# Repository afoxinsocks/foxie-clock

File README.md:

# Foxie Clock

## A Nixie-like, retro, RGB LED, Arduino-powered clock

Welcome to the Foxie Clock, a fully open-source RGB clock with nixie-like edge-lit acrylic digits. Or... an RGB pixel display clock, if you like!

## Looks

With a look inspired by old nixie tubes and with capacitors protruding through the surface like vacuum tubes, the Foxie Clock is a fun, colorful way to display the time at your desk, office, or anywhere. Brightness, color, and time are all adjustable directly with 4 buttons on the back. [Using the clock is very easy](USAGE.md), with 4 buttons on the back providing various functionality for setting time, animation modes, colors, and brightness, 12/24h mode, PXL mode, and more.

# [Get your own](https://www.foxieproducts.com/)

Head [over to Foxie Products](https://www.foxieproducts.com/) to order your own Foxie Clock kit.

## 3D Print your own case or modify it yourself!

All .STL models and the full Fusion360 project and the .step files are also available for anyone wanting to make changes to the design more easily. Head over to [Thingiverse](https://www.thingiverse.com/thing:4114349) to download.

## Easy to assemble

The clock is [easy to assemble](ASSEMBLY.md) and looks beautiful when complete.

The case is 3D printed and is included with the kit.

The circuit board can be ordered fully soldered, or if you like, you can solder the 4 buttons and RedBoard Nano yourself, using the plentiful pictures in the [electronics assembly guide](ELECTRONICS.md).

## Easy to hack

The Foxie Clock is powered by a SparkFun RedBoard Artemis Nano (https://www.sparkfun.com/products/15443), an extremely cool, fully Arduino-compatible board that supports Bluetooth LE 5.0 and much, much more. It is included in every Foxie Clock kit, along with everything you need (including USB-C cable) to get running.

## Fully Open Source

The Foxie Clock PCB and firmware were developed using Open Source software. The source code, laser cutting files, PCB design, and documentation for assembly are all freely available here.

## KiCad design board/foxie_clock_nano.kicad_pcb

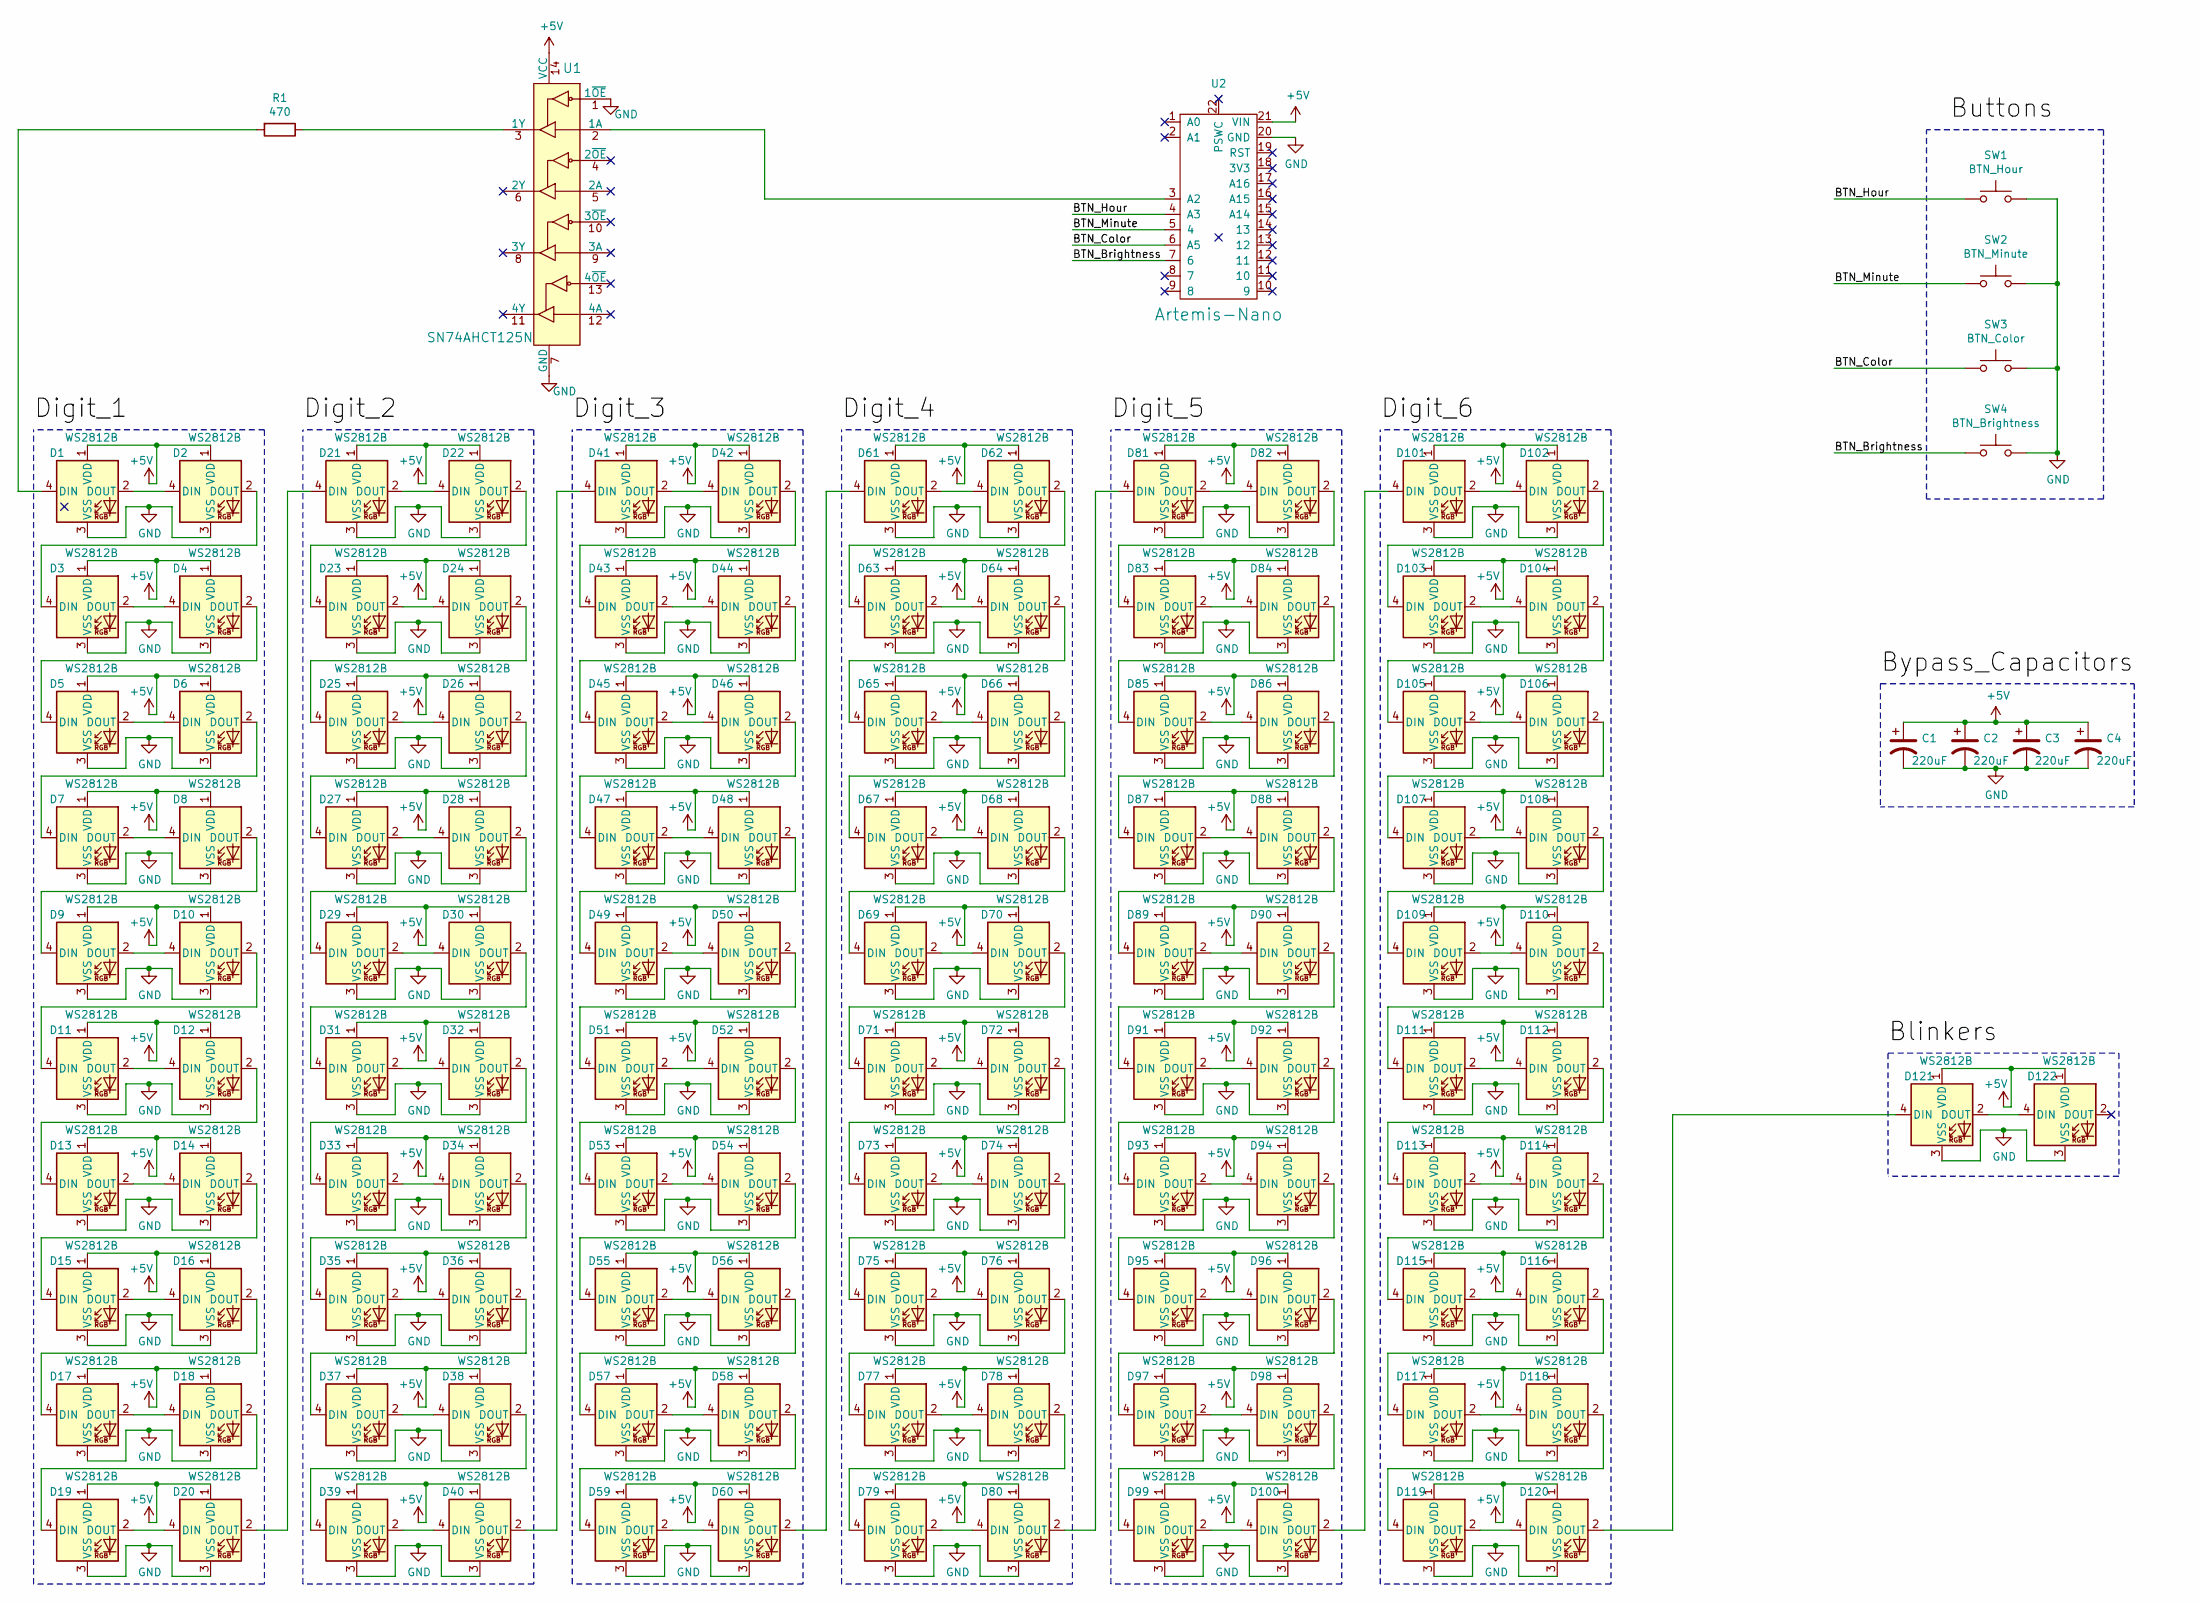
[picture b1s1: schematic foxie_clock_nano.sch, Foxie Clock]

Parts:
C1, C2, C3, C4: 220uF; CP_Elec_6.3x7.7; LCSC C127327
D1, D2, D3, D4, D5, D6, D7, D8, D9, D10, D11, D12, D13, D14, D15, D16, D17, D18, D19, D20, D21, D22, D23, D24, D25, D26, D27, D28, D29, D30, D31, D32, D33, D34, D35, D36, D37, D38, D39, D40, D41, D42, D43, D44, D45, D46, D47, D48, D49, D50, D51, D52, D53, D54, D55, D56, D57, D58, D59, D60, D61, D62, D63, D64, D65, D66, D67, D68, D69, D70, D71, D72, D73, D74, D75, D76, D77, D78, D79, D80, D81, D82, D83, D84, D85, D86, D87, D88, D89, D90, D91, D92, D93, D94, D95, D96, D97, D98, D99, D100, D101, D102, D103, D104, D105, D106, D107, D108, D109, D110, D111, D112, D113, D114, D115, D116, D117, D118, D119, D120, D121, D122: WS2812B; LED_WS2812B_PLCC4_5.0x5.0mm_P3.2mm; LCSC C114586
R1: 470; R_1206_3216Metric; LCSC C25383
SW1: BTN_Hour; SW_Tactile_SPST_Angled_PTS645Vx58-2LFS
SW2: BTN_Minute; SW_Tactile_SPST_Angled_PTS645Vx58-2LFS
SW3: BTN_Color; SW_Tactile_SPST_Angled_PTS645Vx58-2LFS
SW4: BTN_Brightness; SW_Tactile_SPST_Angled_PTS645Vx58-2LFS
U1: SN74AHCT125N; TSSOP-14_4.4x5mm_P0.65mm; LCSC C36365
U2: Artemis-Nano

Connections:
+5V: C1.1, C2.1, C3.1, C4.1, D1.1 (VDD), D2.1 (VDD), D3.1 (VDD), D4.1 (VDD), D5.1 (VDD), D6.1 (VDD), D7.1 (VDD), D8.1 (VDD), D9.1 (VDD), D10.1 (VDD), D11.1 (VDD), D12.1 (VDD), D13.1 (VDD), D14.1 (VDD), D15.1 (VDD), D16.1 (VDD), D17.1 (VDD), D18.1 (VDD), D19.1 (VDD), D20.1 (VDD), D21.1 (VDD), D22.1 (VDD), D23.1 (VDD), D24.1 (VDD), D25.1 (VDD), D26.1 (VDD), D27.1 (VDD), D28.1 (VDD), D29.1 (VDD), D30.1 (VDD), D31.1 (VDD), D32.1 (VDD), D33.1 (VDD), D34.1 (VDD), D35.1 (VDD), D36.1 (VDD), D37.1 (VDD), D38.1 (VDD), D39.1 (VDD), D40.1 (VDD), D41.1 (VDD), D42.1 (VDD), D43.1 (VDD), D44.1 (VDD), D45.1 (VDD), D46.1 (VDD), D47.1 (VDD), D48.1 (VDD), D49.1 (VDD), D50.1 (VDD), D51.1 (VDD), D52.1 (VDD), D53.1 (VDD), D54.1 (VDD), D55.1 (VDD), D56.1 (VDD), D57.1 (VDD), D58.1 (VDD), D59.1 (VDD), D60.1 (VDD), D61.1 (VDD), D62.1 (VDD), D63.1 (VDD), D64.1 (VDD), D65.1 (VDD), D66.1 (VDD), D67.1 (VDD), D68.1 (VDD), D69.1 (VDD), D70.1 (VDD), D71.1 (VDD), D72.1 (VDD), D73.1 (VDD), D74.1 (VDD), D75.1 (VDD), D76.1 (VDD), D77.1 (VDD), D78.1 (VDD), D79.1 (VDD), D80.1 (VDD), D81.1 (VDD), D82.1 (VDD), D83.1 (VDD), D84.1 (VDD), D85.1 (VDD), D86.1 (VDD), D87.1 (VDD), D88.1 (VDD), D89.1 (VDD), D90.1 (VDD), D91.1 (VDD), D92.1 (VDD), D93.1 (VDD), D94.1 (VDD), D95.1 (VDD), D96.1 (VDD), D97.1 (VDD), D98.1 (VDD), D99.1 (VDD), D100.1 (VDD), D101.1 (VDD), D102.1 (VDD), D103.1 (VDD), D104.1 (VDD), D105.1 (VDD), D106.1 (VDD), D107.1 (VDD), D108.1 (VDD), D109.1 (VDD), D110.1 (VDD), D111.1 (VDD), D112.1 (VDD), D113.1 (VDD), D114.1 (VDD), D115.1 (VDD), D116.1 (VDD), D117.1 (VDD), D118.1 (VDD), D119.1 (VDD), D120.1 (VDD), D121.1 (VDD), D122.1 (VDD), U1.14 (VCC), U2.21 (VIN)
/BTN_Brightness: SW4.1, U2.7 (6)
/BTN_Color: SW3.1, U2.6 (A5)
/BTN_Hour: SW1.1, U2.4 (A3)
/BTN_Minute: SW2.1, U2.5 (4)
GND: C1.2, C2.2, C3.2, C4.2, D1.3 (VSS), D2.3 (VSS), D3.3 (VSS), D4.3 (VSS), D5.3 (VSS), D6.3 (VSS), D7.3 (VSS), D8.3 (VSS), D9.3 (VSS), D10.3 (VSS), D11.3 (VSS), D12.3 (VSS), D13.3 (VSS), D14.3 (VSS), D15.3 (VSS), D16.3 (VSS), D17.3 (VSS), D18.3 (VSS), D19.3 (VSS), D20.3 (VSS), D21.3 (VSS), D22.3 (VSS), D23.3 (VSS), D24.3 (VSS), D25.3 (VSS), D26.3 (VSS), D27.3 (VSS), D28.3 (VSS), D29.3 (VSS), D30.3 (VSS), D31.3 (VSS), D32.3 (VSS), D33.3 (VSS), D34.3 (VSS), D35.3 (VSS), D36.3 (VSS), D37.3 (VSS), D38.3 (VSS), D39.3 (VSS), D40.3 (VSS), D41.3 (VSS), D42.3 (VSS), D43.3 (VSS), D44.3 (VSS), D45.3 (VSS), D46.3 (VSS), D47.3 (VSS), D48.3 (VSS), D49.3 (VSS), D50.3 (VSS), D51.3 (VSS), D52.3 (VSS), D53.3 (VSS), D54.3 (VSS), D55.3 (VSS), D56.3 (VSS), D57.3 (VSS), D58.3 (VSS), D59.3 (VSS), D60.3 (VSS), D61.3 (VSS), D62.3 (VSS), D63.3 (VSS), D64.3 (VSS), D65.3 (VSS), D66.3 (VSS), D67.3 (VSS), D68.3 (VSS), D69.3 (VSS), D70.3 (VSS), D71.3 (VSS), D72.3 (VSS), D73.3 (VSS), D74.3 (VSS), D75.3 (VSS), D76.3 (VSS), D77.3 (VSS), D78.3 (VSS), D79.3 (VSS), D80.3 (VSS), D81.3 (VSS), D82.3 (VSS), D83.3 (VSS), D84.3 (VSS), D85.3 (VSS), D86.3 (VSS), D87.3 (VSS), D88.3 (VSS), D89.3 (VSS), D90.3 (VSS), D91.3 (VSS), D92.3 (VSS), D93.3 (VSS), D94.3 (VSS), D95.3 (VSS), D96.3 (VSS), D97.3 (VSS), D98.3 (VSS), D99.3 (VSS), D100.3 (VSS), D101.3 (VSS), D102.3 (VSS), D103.3 (VSS), D104.3 (VSS), D105.3 (VSS), D106.3 (VSS), D107.3 (VSS), D108.3 (VSS), D109.3 (VSS), D110.3 (VSS), D111.3 (VSS), D112.3 (VSS), D113.3 (VSS), D114.3 (VSS), D115.3 (VSS), D116.3 (VSS), D117.3 (VSS), D118.3 (VSS), D119.3 (VSS), D120.3 (VSS), D121.3 (VSS), D122.3 (VSS), SW1.2, SW2.2, SW3.2, SW4.2, U1.1 (1~OE), U1.7 (GND), U2.20 (GND)
unnamed: D1.2 (DOUT), D2.4 (DIN)
unnamed: D1.4 (DIN), R1.2
unnamed: D2.2 (DOUT), D3.4 (DIN)
unnamed: D3.2 (DOUT), D4.4 (DIN)
unnamed: D4.2 (DOUT), D5.4 (DIN)
unnamed: D5.2 (DOUT), D6.4 (DIN)
unnamed: D6.2 (DOUT), D7.4 (DIN)
unnamed: D7.2 (DOUT), D8.4 (DIN)
unnamed: D8.2 (DOUT), D9.4 (DIN)
unnamed: D10.2 (DOUT), D11.4 (DIN)
unnamed: D9.2 (DOUT), D10.4 (DIN)
unnamed: D11.2 (DOUT), D12.4 (DIN)
unnamed: D12.2 (DOUT), D13.4 (DIN)
unnamed: D13.2 (DOUT), D14.4 (DIN)
unnamed: D14.2 (DOUT), D15.4 (DIN)
unnamed: D15.2 (DOUT), D16.4 (DIN)
unnamed: D16.2 (DOUT), D17.4 (DIN)
unnamed: D17.2 (DOUT), D18.4 (DIN)
unnamed: D18.2 (DOUT), D19.4 (DIN)
unnamed: D19.2 (DOUT), D20.4 (DIN)
unnamed: D20.2 (DOUT), D21.4 (DIN)
unnamed: D21.2 (DOUT), D22.4 (DIN)
unnamed: D22.2 (DOUT), D23.4 (DIN)
unnamed: D23.2 (DOUT), D24.4 (DIN)
unnamed: D24.2 (DOUT), D25.4 (DIN)
unnamed: D25.2 (DOUT), D26.4 (DIN)
unnamed: D26.2 (DOUT), D27.4 (DIN)
unnamed: D27.2 (DOUT), D28.4 (DIN)
unnamed: D28.2 (DOUT), D29.4 (DIN)
unnamed: D29.2 (DOUT), D30.4 (DIN)
unnamed: D30.2 (DOUT), D31.4 (DIN)
unnamed: D31.2 (DOUT), D32.4 (DIN)
unnamed: D32.2 (DOUT), D33.4 (DIN)
unnamed: D33.2 (DOUT), D34.4 (DIN)
unnamed: D34.2 (DOUT), D35.4 (DIN)
unnamed: D35.2 (DOUT), D36.4 (DIN)
unnamed: D36.2 (DOUT), D37.4 (DIN)
unnamed: D37.2 (DOUT), D38.4 (DIN)
unnamed: D38.2 (DOUT), D39.4 (DIN)
unnamed: D39.2 (DOUT), D40.4 (DIN)
unnamed: D40.2 (DOUT), D41.4 (DIN)
unnamed: D41.2 (DOUT), D42.4 (DIN)
unnamed: D42.2 (DOUT), D43.4 (DIN)
unnamed: D43.2 (DOUT), D44.4 (DIN)
unnamed: D44.2 (DOUT), D45.4 (DIN)
unnamed: D45.2 (DOUT), D46.4 (DIN)
unnamed: D46.2 (DOUT), D47.4 (DIN)
unnamed: D47.2 (DOUT), D48.4 (DIN)
unnamed: D48.2 (DOUT), D49.4 (DIN)
unnamed: D49.2 (DOUT), D50.4 (DIN)
unnamed: D50.2 (DOUT), D51.4 (DIN)
unnamed: D51.2 (DOUT), D52.4 (DIN)
unnamed: D52.2 (DOUT), D53.4 (DIN)
unnamed: D53.2 (DOUT), D54.4 (DIN)
unnamed: D54.2 (DOUT), D55.4 (DIN)
unnamed: D55.2 (DOUT), D56.4 (DIN)
unnamed: D56.2 (DOUT), D57.4 (DIN)
unnamed: D57.2 (DOUT), D58.4 (DIN)
unnamed: D58.2 (DOUT), D59.4 (DIN)
unnamed: D59.2 (DOUT), D60.4 (DIN)
unnamed: D60.2 (DOUT), D61.4 (DIN)
unnamed: D61.2 (DOUT), D62.4 (DIN)
unnamed: D62.2 (DOUT), D63.4 (DIN)
unnamed: D63.2 (DOUT), D64.4 (DIN)
unnamed: D64.2 (DOUT), D65.4 (DIN)
unnamed: D65.2 (DOUT), D66.4 (DIN)
unnamed: D66.2 (DOUT), D67.4 (DIN)
unnamed: D67.2 (DOUT), D68.4 (DIN)
unnamed: D68.2 (DOUT), D69.4 (DIN)
unnamed: D69.2 (DOUT), D70.4 (DIN)
unnamed: D70.2 (DOUT), D71.4 (DIN)
unnamed: D71.2 (DOUT), D72.4 (DIN)
unnamed: D72.2 (DOUT), D73.4 (DIN)
unnamed: D73.2 (DOUT), D74.4 (DIN)
unnamed: D74.2 (DOUT), D75.4 (DIN)
unnamed: D75.2 (DOUT), D76.4 (DIN)
unnamed: D76.2 (DOUT), D77.4 (DIN)
unnamed: D77.2 (DOUT), D78.4 (DIN)
unnamed: D78.2 (DOUT), D79.4 (DIN)
unnamed: D79.2 (DOUT), D80.4 (DIN)
unnamed: D80.2 (DOUT), D81.4 (DIN)
unnamed: D81.2 (DOUT), D82.4 (DIN)
unnamed: D82.2 (DOUT), D83.4 (DIN)
unnamed: D83.2 (DOUT), D84.4 (DIN)
unnamed: D84.2 (DOUT), D85.4 (DIN)
unnamed: D85.2 (DOUT), D86.4 (DIN)
unnamed: D86.2 (DOUT), D87.4 (DIN)
unnamed: D87.2 (DOUT), D88.4 (DIN)
unnamed: D88.2 (DOUT), D89.4 (DIN)
unnamed: D89.2 (DOUT), D90.4 (DIN)
unnamed: D90.2 (DOUT), D91.4 (DIN)
unnamed: D91.2 (DOUT), D92.4 (DIN)
unnamed: D92.2 (DOUT), D93.4 (DIN)
unnamed: D93.2 (DOUT), D94.4 (DIN)
unnamed: D94.2 (DOUT), D95.4 (DIN)
unnamed: D95.2 (DOUT), D96.4 (DIN)
unnamed: D96.2 (DOUT), D97.4 (DIN)
unnamed: D97.2 (DOUT), D98.4 (DIN)
unnamed: D98.2 (DOUT), D99.4 (DIN)
unnamed: D100.2 (DOUT), D101.4 (DIN)
unnamed: D99.2 (DOUT), D100.4 (DIN)
unnamed: D101.2 (DOUT), D102.4 (DIN)
unnamed: D102.2 (DOUT), D103.4 (DIN)
unnamed: D103.2 (DOUT), D104.4 (DIN)
unnamed: D104.2 (DOUT), D105.4 (DIN)
unnamed: D105.2 (DOUT), D106.4 (DIN)
unnamed: D106.2 (DOUT), D107.4 (DIN)
unnamed: D107.2 (DOUT), D108.4 (DIN)
unnamed: D108.2 (DOUT), D109.4 (DIN)
unnamed: D109.2 (DOUT), D110.4 (DIN)
unnamed: D110.2 (DOUT), D111.4 (DIN)
unnamed: D111.2 (DOUT), D112.4 (DIN)
unnamed: D112.2 (DOUT), D113.4 (DIN)
unnamed: D113.2 (DOUT), D114.4 (DIN)
unnamed: D114.2 (DOUT), D115.4 (DIN)
unnamed: D115.2 (DOUT), D116.4 (DIN)
unnamed: D116.2 (DOUT), D117.4 (DIN)
unnamed: D117.2 (DOUT), D118.4 (DIN)
unnamed: D118.2 (DOUT), D119.4 (DIN)
unnamed: D119.2 (DOUT), D120.4 (DIN)
unnamed: D120.2 (DOUT), D121.4 (DIN)
unnamed: D121.2 (DOUT), D122.4 (DIN)
unnamed: R1.1, U1.3 (1Y)
unnamed: U1.2 (1A), U2.3 (A2)

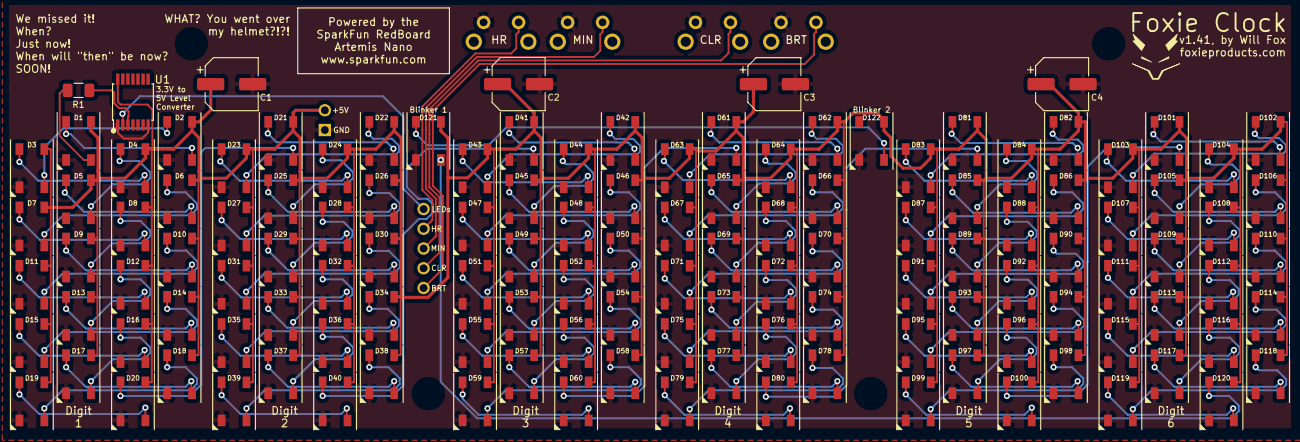
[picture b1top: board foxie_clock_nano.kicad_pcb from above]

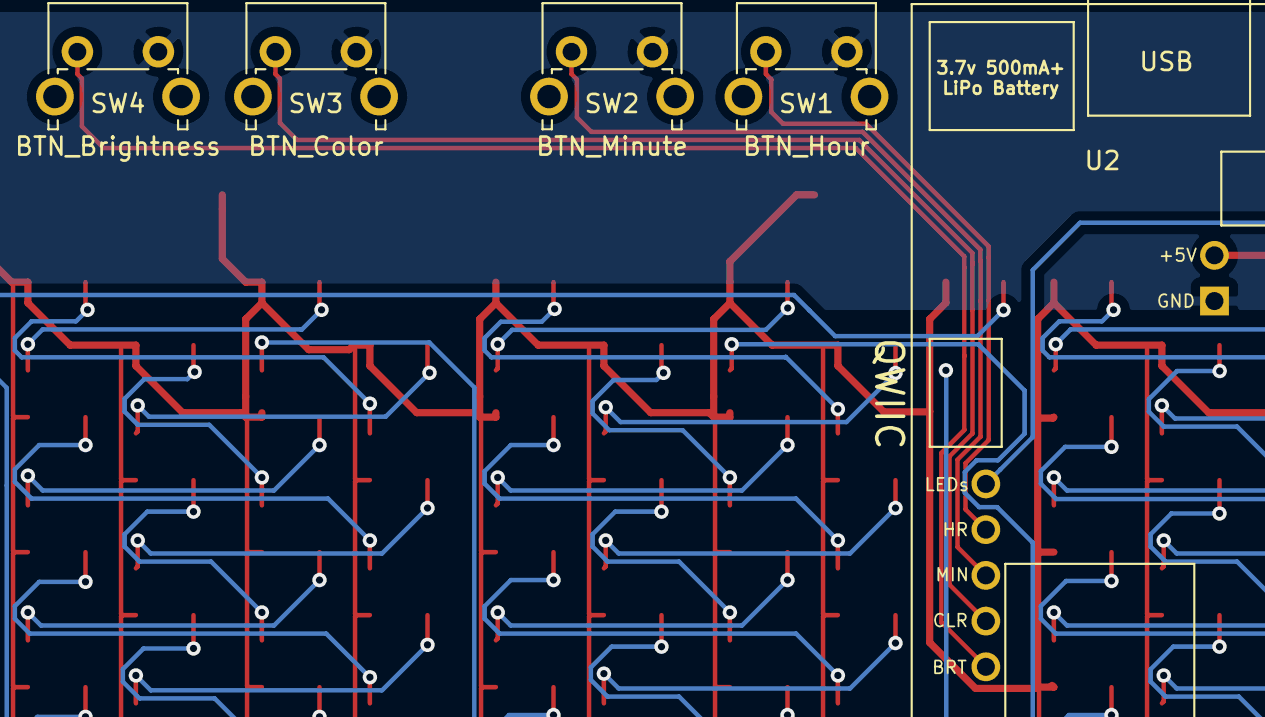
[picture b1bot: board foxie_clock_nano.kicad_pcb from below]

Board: 2 copper layers, 133 parts (5 on the bottom side), 130 nets.

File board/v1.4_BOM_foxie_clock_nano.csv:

Comment,Designator,Footprint,LCSC, LCSC
"220uF","C1,C2,C3,C4","Capacitor_SMD:CP_Elec_6.3x7.7","","C127327"
"WS2812B","D2,D1,D4,D3,D6,D5,D9,D10,D7,D8,D12,D11,D14,D13,D16,D15,D19,D20,D17,D18,D22,D21,D24,D23,D26,D25,D29,D30,D27,D28,D32,D31,D34,D33,D36,D35,D39,D40,D37,D38,D42,D41,D44,D43,D46,D45,D49,D50,D47,D48,D52,D51,D54,D53,D56,D55,D59,D60,D57,D58,D62,D61,D64,D63,D66,D65,D69,D70,D67,D68,D72,D71,D74,D73,D76,D75,D79,D80,D77,D78,D82,D81,D84,D83,D86,D85,D89,D90,D87,D88,D92,D91,D94,D93,D96,D95,D99,D100,D97,D98,D102,D101,D104,D103,D106,D105,D109,D110,D107,D108,D112,D111,D114,D113,D116,D115,D119,D120,D117,D118,D122,D121","foxie_clock_nano:LED_WS2812B_PLCC4_5.0x5.0mm_P3.2mm","","C114586"
"470","R1","Resistor_SMD:R_1206_3216Metric","","C25383"
"BTN_Hour","SW1","Button_Switch_THT:SW_Tactile_SPST_Angled_PTS645Vx58-2LFS",""
"BTN_Minute","SW2","Button_Switch_THT:SW_Tactile_SPST_Angled_PTS645Vx58-2LFS",""
"BTN_Color","SW3","Button_Switch_THT:SW_Tactile_SPST_Angled_PTS645Vx58-2LFS",""
"BTN_Brightness","SW4","Button_Switch_THT:SW_Tactile_SPST_Angled_PTS645Vx58-2LFS",""
"SN74AHCT125N","U1","Package_SO:TSSOP-14_4.4x5mm_P0.65mm","","C36365"
"Artemis-Nano","U2","foxie_clock_nano:Artemis-Nano",""

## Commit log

2020-01-04 Adding KiCad files for 1.4 board
2020-01-04 Adding .gitignore file and removing .DS_Store
2020-01-11 Adding initial firmware files using csonsino's early Neopixel apollo3 support
2020-01-11 Abstracting apollo3-specific RTC code
2020-01-11 Cleanup, primarily moving BLE-specific things into ble_funcs.cpp
2020-01-11 Improving timing to eliminate occasional green first LED
2020-01-11 Cleanup, renaming, and more
2020-01-12 Rudimentary ability to set time via BT using Immediate Alert levels... SparkFun's BLE support is not quite there yet.
2020-01-12 Cleanup, update clock only after seconds have been received
2020-01-12 More cleanup, add 400ms wait on boot for BLE hardware to come up properly
2020-01-12 Cleanup
2020-01-12 Disabling debug output
2020-01-12 Add slight delay in timing to hopefully resolve occasional bad pixel color... really need a better solution
2020-01-14 Another timing tweak to fix rare wrong color LEDs... until better method is implemented.
2020-01-14 Default to 0:00:00 when plugging in, instead of compiler time.
2020-01-14 Removing .step file in favor of updated .step file to be on thingiverse
2020-01-14 Removing backup KiCad PCB from source control
2020-01-14 Adding acrylic digit SVG files
2020-01-14 Adding acrylic lid SVG files, one for 1.5mm and one for 1.65mm holes
2020-01-14 Adding Settings class, not yet used.
2020-01-16 Lots of cleanup and changes to move toward runtime settings adjustments
2020-01-18 Enable settings use for all values and remove ifdefs for compile time settings changes
2020-01-18 Remove RTC time change on boot
2020-01-18 More timing tweaks until I have time to move this entire setup to a better solution
2020-01-18 Updates to remove color setting from digit manager
2020-01-18 Button cleanup, refactored debouncing logic and switched to callback lambda functions for button events
2020-01-18 Much improved button debouncing and handler setup, with press, repeat, and release events
2020-01-18 Button behavior improvements: Hour button must be held for 1s to enter/exit 'Set Time' mode.
2020-01-18 Separating Clock class into clock.hpp
2020-01-18 Adding Animator class and refactoring Settings for static Get/Set/Save use
2020-01-18 Add very basic glowing animator
2020-01-18 Added set time animator
2020-01-18 Detect out-of-range default EEPROM values and reset to defaults
2020-01-18 Refactor Bluetooth command handling and move to separate cmd_handler.hpp file
2020-01-18 Add ability to change settings from Bluetooth commands
2020-01-19 Reformatting all source files using clang-format 'Microsoft' style
2020-01-19 Fix compile issue caused by header file reorganization due to clang formatting
2020-01-19 Cleanup, switching naked pointers to shared_ptr
2020-01-19 Updating lid laser cutting SVG files
2020-01-19 Renaming acrylic to laser_cutting
2020-01-21 Adding images for assembly
2020-01-21 Adding image for assembled, powered-on clock
2020-01-21 Adding a few more images for the main page
2020-01-21 Adding pixel display image
2020-01-21 Removing black border from PCB render
2020-01-21 Rotating tools image.
2020-01-22 Removing step 7b image
2020-01-22 Rotating several more images
2020-01-22 Adding Tindie store links... eeek!
2020-01-22 Adding missing step to select the correct Board
2020-01-28 Increasing laser cut width to 5.1mm to account for minor inconsistencies and make tolerance less tight
2020-02-02 Change default setting type to be edge lit for kits
2020-02-10 Add a couple of example lines for changing the animation mode
2020-02-11 Add minimum time before repeat begins
2020-02-11 Add new ANIM_CYCLE_FLOW_LEFT animation type, allow repeat for Minute button for setting time
2020-02-11 Flow animation should redraw when re-entering normal clock mode
2020-02-11 Rename confusingly named RedrawIfNeeded function to Draw and improve set time mode to set again on exit so that the seconds stick
2020-02-11 Add functionality for M button to cycle animation types
2020-02-11 Update USAGE.md
    Add animation mode button documentation
2020-02-11 Fix broken digit blinker separators
2020-02-14 Crop case renders
2020-02-15 Adding professional image of clock
2020-02-23 Added support for DC3231 battery backup clock module
2020-02-24 Moved DS3231 modifications to rtc_hal_apollo3.cpp
2020-02-24 bugs....
2020-02-24 resolved silly bugs
2020-02-24 Minor changes to nbJosh's DS3231 commit to fix formatting and global use. Wire is initialized by default now as well.
2020-02-27 Update INSTALLING.md
    Confirming Sparkfun Apollo3 1.0.29 functionality.
2020-03-01 Update ASSEMBLY.md
    Add the use of a utility knife to lift the edge of the protective paper, and use a fingernail to lift the edge of the internal areas of the "0" and the "8".
2020-03-08 Add some protection against lost BT messages corrupting the state machine
2020-03-08 Fix bug with blinkers staying on between switching display modes from command handler
2020-03-08 Fix bug with animation modes being set way over the maximum and the button not correcting it when pressed, and use Clock::SetBrightness to unify functionality between Brightness button and app contro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
2020-05-06 Adding initial mobile app 1.0 source
2020-07-24 Fix - Changing the animation mode through the app should save settings
2020-07-24 Fix - SparkFun 1.1 SDK changed API
2020-07-24 Fix - Color setting getting way too large. Oops!
2020-07-24 Improve boot-up by delaying Bluetooth init
2020-07-24 Fix - the 7 numeral in pixel mode didn't look quite right
2020-07-24 Animation: Rainbow is added. The "color" button functions as "pause"
2020-07-24 Allow overriding the setPixelColor function
2020-07-24 Add setting for flipping the display, and improve flipping method
2020-07-25 Add RTC hundredth/millis functions
2020-07-25 Add fading transition to changing digits. More fun things on the way!
2020-07-25 Correct an include, thanks @ckirmse
2020-07-30 Minor wording change on PCB
2020-07-30 Edge-lit mode fades should also fade IN the new digit. Pixel mode doesn't look quite right with a fade-in on the new digit so for now, it's excluded.
2020-08-19 Separate step 14 to reduce confusion
2020-08-26 Swap steps 7 and 8, thanks @xuu!
2020-09-09 Moved store to foxieproducts.com!
2020-09-16 Improve Button class to store created buttons This allows a single call to CheckAll() instead of multiple Check()s
2020-09-16 Add 2.5sec long press on M to toggle between EDGE_LIT and PXL mode
2020-09-16 Add sleep mode While holding M, press and release B. The digits will fade out. Press any button to wake up.
2020-12-07 Solve issue with prematurely setting the current button state on change
2020-12-07 Fix issue with setting time interfering with fading transitions
2020-12-13 Back to basics, remove everything except digit display. BLE is gone. Removing BLE because I don't plan to have it in the next version of the clock and I simply have not had the time to work on it or 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
2020-12-13 Cleanup, refactoring.
2020-12-13 More cleanup
2020-12-13 Entirely refactored button handling code
2020-12-13 Bring in the the rest of the changes in Clock
2020-12-13 Brightness, Color, and Toggle buttons are now working.
2020-12-13 Animations are working again and are now owned by the Digit Manager
2020-12-13 Improve behavior when switching between display types
2020-12-13 Cleanup and make Buttons exclusive
2020-12-13 Cleanup, bug fixes in Animators
2020-12-14 Reduce default repeat time slightly
2020-12-14 Annndd fading transitions are back, and better than ever!
2020-12-14 Adding Zippy animation and a bit of cleanup
2020-12-14 Adding Blinkers as new class
2020-12-14 Add ability to flip display by pressing C+B
2020-12-14 Add ability to toggle 24H mode by pressing H+M
2020-12-14 Fix bug with Blinkers turning off LEDs incorrectly, bug fixes mode
2020-12-14 Turn off blinkers before flipping display or switching PXL/Edge lit
2020-12-14 Removing mobile Foxie Clock app developed earlier this year I never had enough time to devote to this application to get it into a releasable state, and I intend to move toward a WebUSB configuration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
2020-12-15 Restore code to clear the EEPROM on a new board.
2020-12-15 Updating digit assembly images
2020-12-15 Adding new primary images
2020-12-17 Improve timing of animations to not be based on rtc_hal_millis.
2020-12-17 Zippy animation only does full digit rollover once per second now.
2020-12-17 Fix issue with off-by-one error causing the settings to reset
2020-12-17 Combine Digits and current/last numbers displayed into struct
2020-12-17 Fix issue with combo buttons not disabling other buttons
2020-12-17 Double the speed the Minute button advances
2020-12-17 Display 12/24H mode when switching
